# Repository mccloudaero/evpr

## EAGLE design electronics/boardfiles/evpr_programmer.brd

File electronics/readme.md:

# Electronics
Electronics design files for EVPR project.

## Contents
* fabrication - Design files for EVPR fabrication processes, including (eventually) full SOPs for each board
* scripts - Scripts used at various points for automating mass alterations to boardfiles
* info - Various human-readable information about the project, including image versions of boardfiles and BOM
* boadfiles - The actual working boardfiles for the EVPR project.

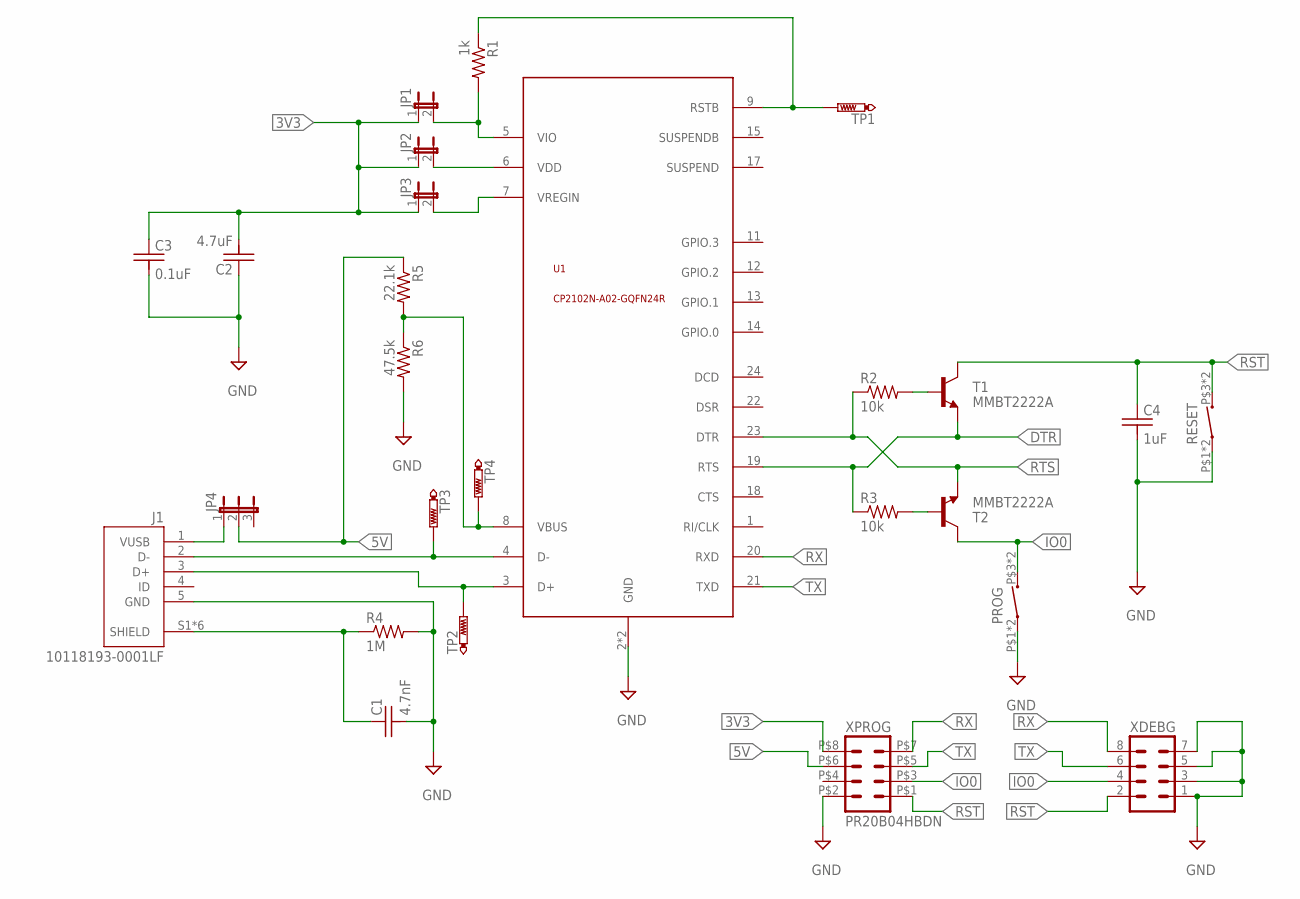
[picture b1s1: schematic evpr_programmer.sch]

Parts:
C1: 4.7nF; C0603
C2: 4.7uF; C0603
C3: 0.1uF; C0603
C4: 1uF; C0603
J1: 10118193-0001LF; FCI_10118193-0001LF
JP1, JP2, JP3: JP1E; JP1
JP4: JP2E; JP2
PROG: MOMENTARY_SWITCH; PTS645
R1: 1k; R0603
R2, R3: 10k; R0603
R4: 1M; R0603
R5: 22.1k; R0603
R6: 47.5k; R0603
RESET: MOMENTARY_SWITCH; PTS645
T1, T2: MMBT2222A; SOT23-BEC
TP1, TP2, TP3, TP4: PTR1TP10R; TP10R
U1: CP2102N-A02-GQFN24R; QFN24-4X4
XDEBG: MA04-2
XPROG: PR20B04HBDN

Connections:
3V3: C2.2, C3.1, JP1.1, JP2.1, JP3.1, XPROG.P$8 (8)
5V: JP4.2, R5.1, XPROG.P$6 (6)
DTR: R3.1, T1.E, U1.19 (RTS)
GND: C1.2, C2.1, C3.2, C4.2, J1.5 (GND), PROG.P$1 (1), PROG.P$2 (1), R4.2, R6.2, RESET.P$1 (1), RESET.P$2 (1), U1.2 (GND), U1.EXP (GND), XDEBG.1, XDEBG.3, XDEBG.5, XDEBG.7, XPROG.P$2 (2)
IO0: PROG.P$3 (2), PROG.P$4 (2), T2.C, XDEBG.4, XPROG.P$3 (3)
unnamed: J1.1 (VUSB), JP4.1
unnamed: JP2.2, U1.6 (VDD)
unnamed: R1.1, TP1.TP, U1.9 (RSTB)
unnamed: JP1.2, R1.2, U1.5 (VIO)
unnamed: C1.1, J1.S1 (SHIELD), J1.S2 (SHIELD), J1.S3 (SHIELD), J1.S4 (SHIELD), J1.S5 (SHIELD), J1.S6 (SHIELD), R4.1
unnamed: R3.2, T2.B
unnamed: R2.2, T1.B
unnamed: J1.3 (D+), TP2.TP, U1.3 (D+)
unnamed: J1.2 (D-), TP3.TP, U1.4 (D-)
unnamed: JP3.2, U1.7 (VREGIN)
unnamed: R5.2, R6.1, TP4.TP, U1.8 (VBUS)
RST: C4.1, RESET.P$3 (2), RESET.P$4 (2), T1.C, XDEBG.2, XPROG.P$1 (1)
RTS: R2.1, T2.E, U1.23 (DTR)
RX: U1.20 (RXD), XDEBG.8, XPROG.P$7 (7)
TX: U1.21 (TXD), XDEBG.6, XPROG.P$5 (5)

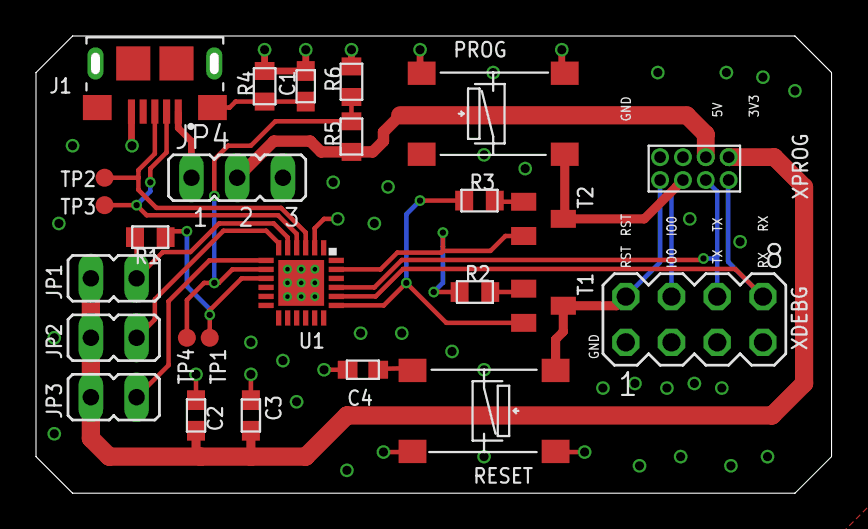
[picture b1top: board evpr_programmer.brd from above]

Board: 2 copper layers, 44.2 x 25.4 mm, 26 parts (0 on the bottom side), 20 nets.

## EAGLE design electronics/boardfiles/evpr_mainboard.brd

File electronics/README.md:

# EVPR electronics

# Compile Notes
Requires ESP-IDF commit (or later):

commit e6afe28bafe5db5ab79fae213f2e8e1ccd9f937c
Merge: ca7da78 7370f29
Author: Jeroen Domburg <jeroen@espressif.com>
Date:   Fri Sep 29 11:20:04 2017 +0800

    Merge branch 'test/unity_print' into 'master'
    
    test: update the format of TEST_ASSERT macro series in ``unity.c``
    
    See merge request !1327

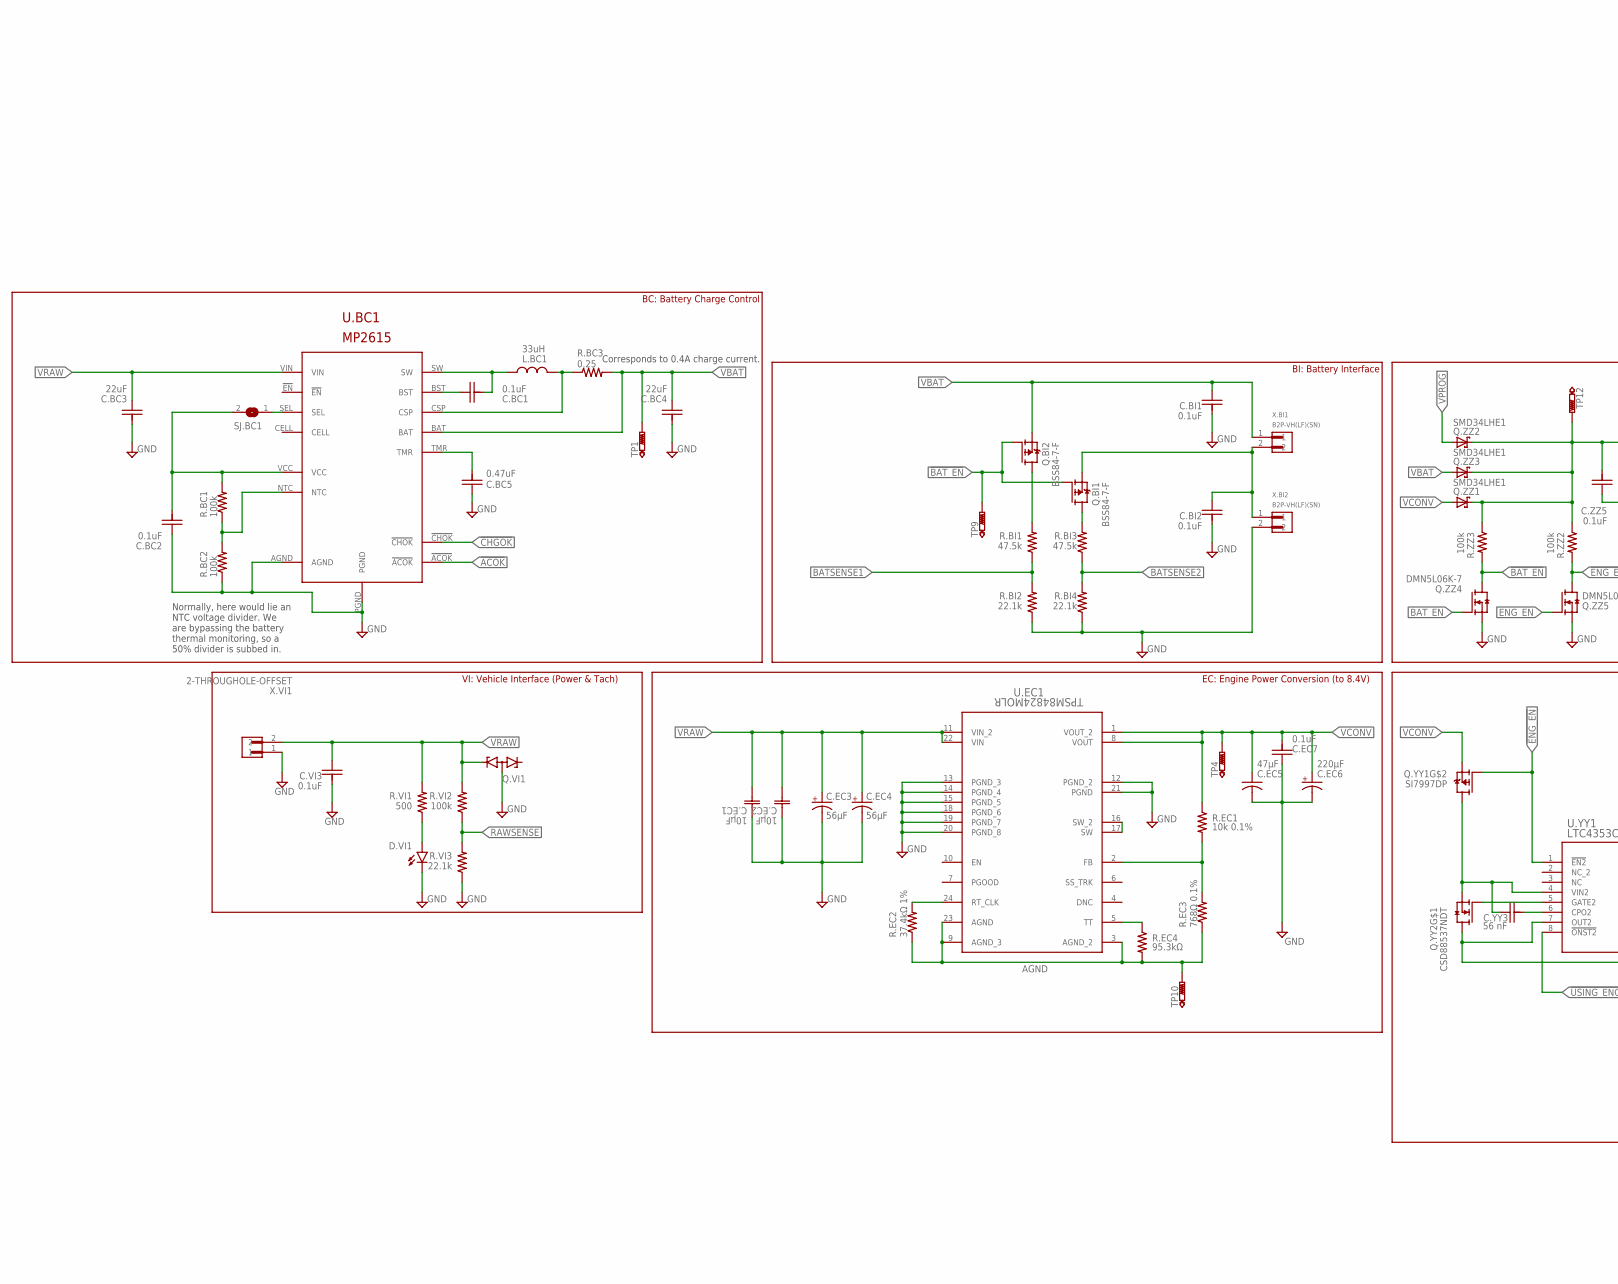
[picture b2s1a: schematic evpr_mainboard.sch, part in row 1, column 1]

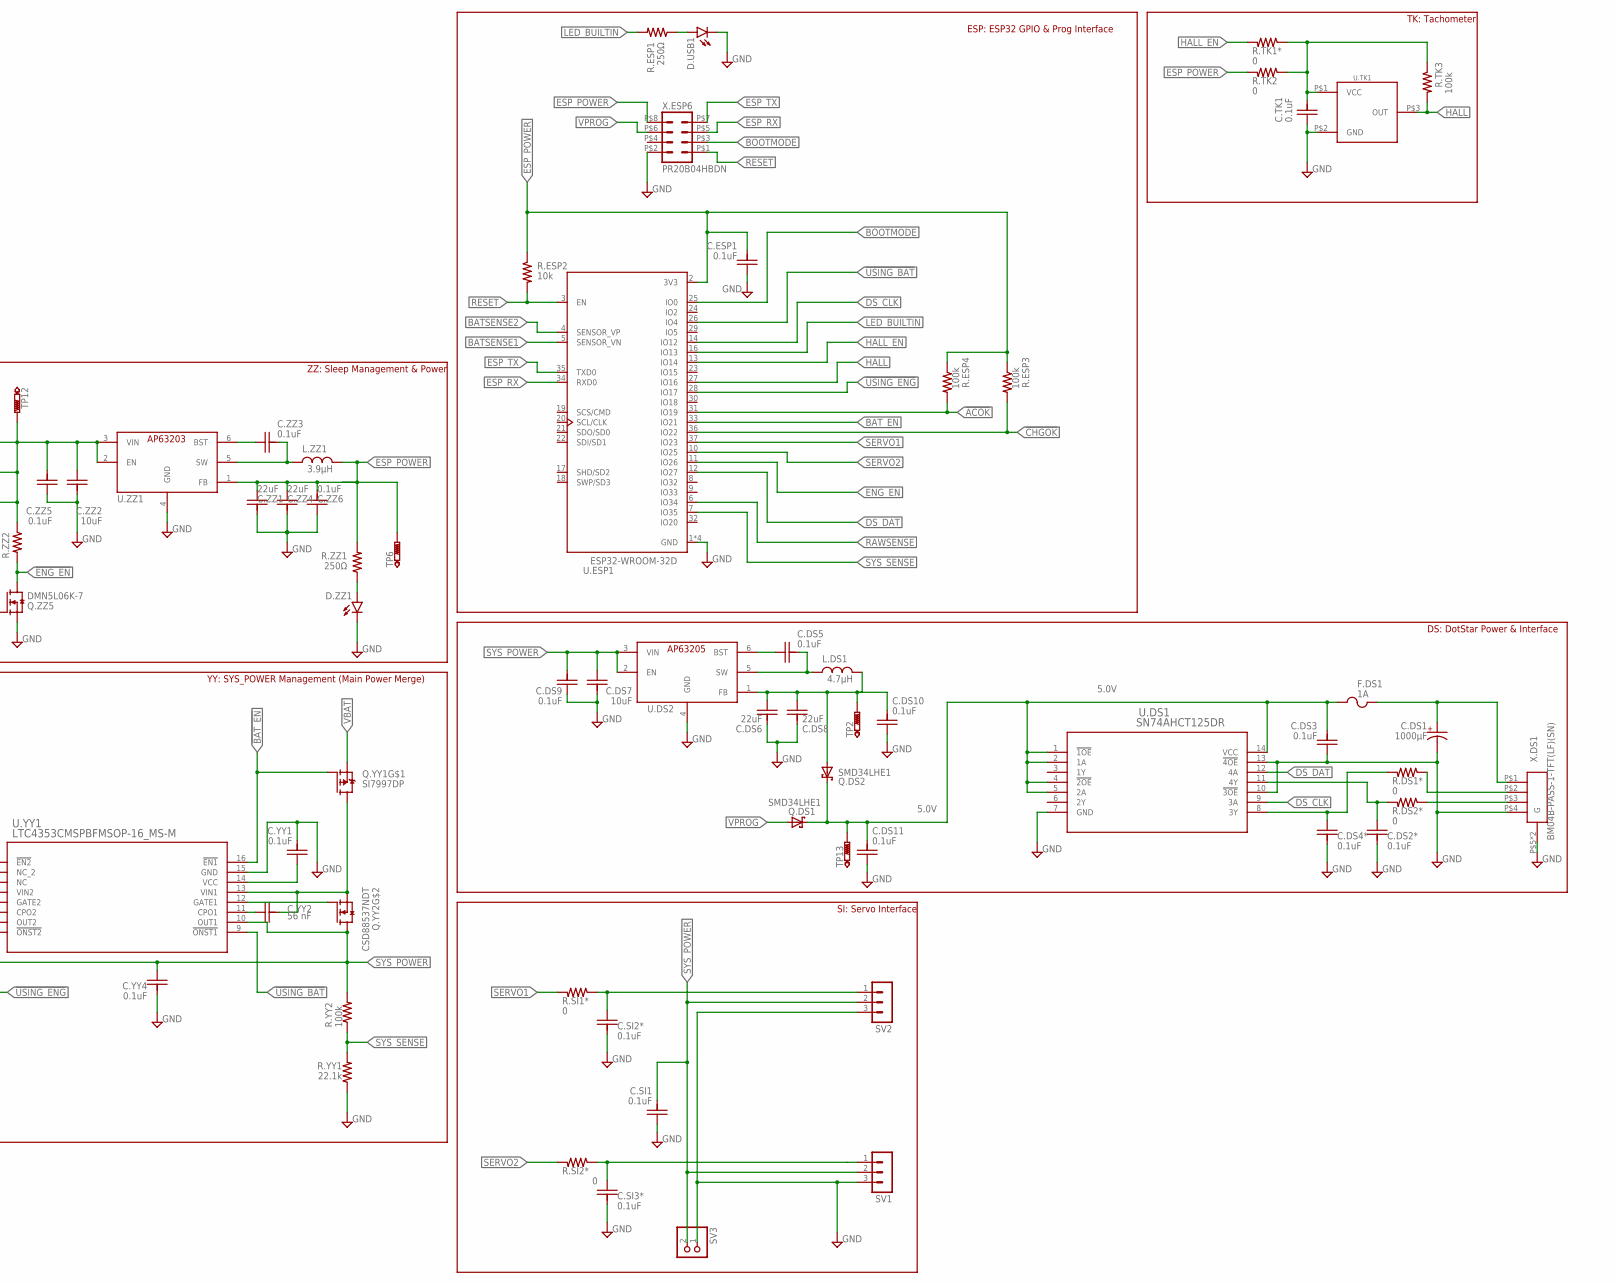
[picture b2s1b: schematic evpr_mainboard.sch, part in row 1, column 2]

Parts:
C.BC1, C.BC2, C.BI1, C.BI2, C.DS2*, C.DS3, C.DS4*, C.DS5, C.DS9, C.DS10, C.DS11, C.EC7, C.ESP1, C.SI1, C.SI2*, C.SI3*, C.TK1, C.VI3, C.YY1, C.YY4, C.ZZ3, C.ZZ5, C.ZZ6: 0.1uF; C0603
C.BC3, C.BC4, C.DS6, C.DS8, C.ZZ1, C.ZZ4: 22uF; C0603
C.BC5: 0.47uF; C0603
C.DS1: 1000µF; 810RADCAN
C.DS7, C.ZZ2: 10uF; C0603
C.EC1, C.EC2: 10µF; CAP_3225
C.EC3, C.EC4: 56µF; OSCON_SVPF_6.3MM
C.EC5: 47µF; C1210
C.EC6: 220µF; C6CYLCAP
C.YY2, C.YY3: 56 nF; C0603
D.USB1, D.VI1, D.ZZ1: LEDCHIP-LED0805; CHIP-LED0805
F.DS1: 1A; C1-M
L.BC1: 33uH; SRN5040TA
L.DS1: 4.7µH; SRR4818A-XXXX
L.ZZ1: 3.9µH; SRR4818A-XXXX
Q.BI1, Q.BI2: BSS84-7-F; SOT23
Q.DS1, Q.DS2, Q.ZZ1, Q.ZZ2, Q.ZZ3: SMD34LHE1; SOD-123HE1
Q.VI1: VESD16A2-03G-G3-08; SOT23
Q.YY1: SI7997DP; POWERPAK_SO8DUAL
Q.YY2: CSD88537NDT; SOIC8
Q.ZZ4, Q.ZZ5: DMN5L06K-7; SOT23
R.BC1, R.BC2, R.ESP3, R.ESP4, R.TK3, R.VI2, R.YY2, R.ZZ2, R.ZZ3: 100k; R0603
R.BC3: 0.25; R0603
R.BI1, R.BI3: 47.5k; R0603
R.BI2, R.BI4, R.VI3, R.YY1: 22.1k; R0603
R.DS1*, R.DS2*, R.SI1*, R.SI2*, R.TK1*, R.TK2: 0; R0603
R.EC1: 10k 0.1%; R0603
R.EC2: 37.4kΩ 1%; R0603
R.EC3: 768Ω 0.1%; R0603
R.EC4: 95.3kΩ; R0603
R.ESP1, R.ZZ1: 250Ω; R0603
R.ESP2: 10k; R0603
R.VI1: 500; R0603
SJ.BC1: SJ
SV1, SV2: MA03-1
SV3: PINHD-1X2; 1X02
TP1, TP2, TP4, TP6, TP9, TP10, TP12, TP13: PTR1TP10R; TP10R
U.BC1: MP2615; QFN16
U.DS1: SN74AHCT125DR; D14
U.DS2: AP63205; TSOT23-6
U.EC1: TPSM84824MOLR; MOL0024A
U.ESP1: ESP32-WROOM-32D; MODULE_ESP32-WROOM-32D
U.TK1: HALLEFFECT; 1.27MMHALLEFECT
U.YY1: LTC4353CMSPBFMSOP-16_MS-M; MSOP-16_MS-M
U.ZZ1: AP63203; TSOT23-6
X.BI1, X.BI2: B2P-VH(LF)(SN)
X.DS1: BM04B-PASS-1-TFT(LF)(SN)
X.ESP6: PR20B04HBDN
X.VI1: 2-THROUGHOLE-OFFSET; 2-THROUGH-HOLE-LARGE-OFFSET

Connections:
5.0V: C.DS3.2, C.DS11.2, F.DS1.1, Q.DS1.C, Q.DS2.C, TP13.TP, U.DS1.1 (!1OE), U.DS1.2 (1A), U.DS1.4 (!2OE), U.DS1.5 (2A), U.DS1.14 (VCC)
!ACOK: R.ESP4.2, U.BC1.!ACOK, U.ESP1.31 (IO19)
!BAT_EN: Q.BI1.1 (G), Q.BI2.1 (G), Q.YY1.P$2 (G), Q.ZZ4.3 (D), R.ZZ3.2, TP9.TP, U.YY1.16 (!EN1)
!CHGOK: R.ESP3.2, U.BC1.!CHOK, U.ESP1.36 (IO22)
!ENG_EN: Q.YY1.P$4 (G), Q.ZZ5.3 (D), R.ZZ2.2, U.YY1.1 (!EN2)
!USING_BAT: U.ESP1.26 (IO4), U.YY1.9 (!ONST1)
!USING_ENG: U.ESP1.28 (IO17), U.YY1.8 (!ONST2)
AGND: R.EC2.1, R.EC3.1, R.EC4.2, TP10.TP, U.EC1.3 (AGND_2), U.EC1.9 (AGND_3), U.EC1.23 (AGND)
BATSENSE1: R.BI1.1, R.BI2.2, U.ESP1.5 (SENSOR_VN)
BATSENSE2: R.BI3.1, R.BI4.2, U.ESP1.4 (SENSOR_VP)
BAT_EN: Q.ZZ4.1 (G), U.ESP1.33 (IO21)
BOOTMODE: U.ESP1.25 (IO0), X.ESP6.P$3 (3)
DS_CLK: U.DS1.9 (3A), U.ESP1.14 (IO12)
DS_DAT: U.DS1.12 (4A), U.ESP1.12 (IO27)
ENG_EN: Q.ZZ5.1 (G), U.ESP1.11 (IO26)
ESP_POWER: C.ESP1.2, C.ZZ1.1, C.ZZ4.1, C.ZZ6.2, L.ZZ1.P$2 (2), R.ESP2.1, R.ESP3.1, R.ESP4.1, R.TK2.2, R.ZZ1.2, TP6.TP, U.ESP1.2 (3V3), U.ZZ1.1 (FB), X.ESP6.P$8 (8)
ESP_RX: U.ESP1.34 (RXD0), X.ESP6.P$5 (5)
ESP_TX: U.ESP1.35 (TXD0), X.ESP6.P$7 (7)
GND: C.BC2.1, C.BC3.2, C.BC4.2, C.BC5.1, C.BI1.2, C.BI2.2, C.DS1.C$2 (-), C.DS2*.2, C.DS3.1, C.DS4*.2, C.DS6.2, C.DS7.2, C.DS8.2, C.DS9.1, C.DS10.1, C.DS11.1, C.EC1.1, C.EC2.1, C.EC3.-, C.EC4.-, C.EC5.2, C.EC6.P$1 (-), C.EC7.1, C.ESP1.1, C.SI1.1, C.SI2*.2, C.SI3*.2, C.TK1.1, C.VI3.2, C.YY1.2, C.YY4.2, C.ZZ1.2, C.ZZ2.2, C.ZZ4.2, C.ZZ5.1, C.ZZ6.1, D.USB1.C, D.VI1.C, D.ZZ1.C, Q.VI1.3 (AA), Q.ZZ4.2 (S), Q.ZZ5.2 (S), R.BC2.1, R.BI2.1, R.BI4.1, R.VI3.1, R.YY1.1, SV1.3, SV2.3, SV3.1, U.BC1.AGND, U.BC1.PGND, U.DS1.7 (GND), U.DS1.10 (!3OE), U.DS1.13 (!4OE), U.DS2.4 (GND), U.EC1.12 (PGND_2), U.EC1.13 (PGND_3), U.EC1.14 (PGND_4), U.EC1.15 (PGND_5), U.EC1.18 (PGND_6), U.EC1.19 (PGND_7), U.EC1.20 (PGND_8), U.EC1.21 (PGND), U.ESP1.1 (GND), U.ESP1.15 (GND), U.ESP1.38 (GND), U.ESP1.39 (GND), U.TK1.P$2 (GND), U.YY1.15 (GND), U.ZZ1.4 (GND), X.BI2.2, X.DS1.P$4 (4), X.DS1.P$5 (G), X.DS1.P$6 (G), X.ESP6.P$2 (2), X.VI1.1
HALL: R.TK3.2, U.ESP1.27 (IO16), U.TK1.P$3 (OUT)
HALL_EN: R.TK1*.2, U.ESP1.13 (IO14)
LED_BUILTIN: R.ESP1.2, U.ESP1.16 (IO13)
unnamed: C.TK1.2, R.TK1*.1, R.TK2.1, R.TK3.1, U.TK1.P$1 (VCC)
unnamed: R.EC1.2, R.EC3.2, U.EC1.2 (FB)
unnamed: Q.YY2.4 (G), U.YY1.12 (GATE1)
unnamed: C.YY3.1, Q.YY1.D$2A (D), Q.YY2.1 (S), U.YY1.4 (VIN2)
unnamed: C.YY2.2, Q.YY1.D$1B (D), Q.YY2.3 (S), U.YY1.13 (VIN1)
unnamed: C.BC5.2, U.BC1.TMR
unnamed: C.BI2.1, Q.BI1.2 (S), X.BI1.2, X.BI2.1
unnamed: C.ZZ2.1, C.ZZ5.2, Q.ZZ1.C, Q.ZZ2.C, Q.ZZ3.C, R.ZZ2.1, R.ZZ3.1, TP12.TP, U.ZZ1.2 (EN), U.ZZ1.3 (VIN)
unnamed: Q.YY2.2 (G), U.YY1.5 (GATE2)
unnamed: C.SI2*.1, R.SI1*.1, SV2.1
unnamed: C.SI3*.1, R.SI2*.1, SV1.1
unnamed: Q.BI2.3 (D), R.BI1.2
unnamed: C.ZZ3.1, U.ZZ1.6 (BST)
unnamed: U.EC1.16 (SW_2), U.EC1.17 (SW)
unnamed: R.EC2.2, U.EC1.24 (RT_CLK)
unnamed: C.DS2*.1, R.DS2*.2, U.DS1.11 (4Y)
unnamed: D.VI1.A, R.VI1.1
unnamed: D.USB1.A, R.ESP1.1
unnamed: C.ZZ3.2, L.ZZ1.P$1 (1), U.ZZ1.5 (SW)
unnamed: C.DS4*.1, R.DS1*.2, U.DS1.8 (3Y)
unnamed: C.DS1.A$1 (+), F.DS1.2, X.DS1.P$1 (1)
unnamed: C.DS5.1, U.DS2.6 (BST)
unnamed: R.DS1*.1, X.DS1.P$2 (2)
unnamed: R.EC4.1, U.EC1.5 (TT)
unnamed: C.YY1.1, U.YY1.14 (VCC)
unnamed: Q.BI1.3 (D), R.BI3.2
unnamed: D.ZZ1.A, R.ZZ1.1
unnamed: C.YY2.1, U.YY1.11 (CPO1)
unnamed: C.YY3.2, U.YY1.6 (CPO2)
unnamed: R.DS2*.1, X.DS1.P$3 (3)
unnamed: R.BC1.1, R.BC2.2, U.BC1.NTC
unnamed: C.DS5.2, L.DS1.P$1 (1), U.DS2.5 (SW)
unnamed: C.DS6.1, C.DS8.1, C.DS10.2, L.DS1.P$2 (2), Q.DS2.A, TP2.TP, U.DS2.1 (FB)
unnamed: C.BC2.2, R.BC1.2, SJ.BC1.2, U.BC1.VCC
unnamed: L.BC1.P$2 (2), R.BC3.1, U.BC1.CSP
unnamed: SJ.BC1.1, U.BC1.SEL
unnamed: C.BC1.1, U.BC1.BST
unnamed: C.BC1.2, L.BC1.P$1 (1), U.BC1.SW
RAWSENSE: R.VI2.1, R.VI3.2, U.ESP1.6 (IO34)
RESET: R.ESP2.2, U.ESP1.3 (EN), X.ESP6.P$1 (1)
SERVO1: R.SI1*.2, U.ESP1.37 (IO23)
SERVO2: R.SI2*.2, U.ESP1.10 (IO25)
SYS_POWER: C.DS7.1, C.DS9.2, C.SI1.2, C.YY4.1, Q.YY2.5 (D), Q.YY2.6 (D), Q.YY2.7 (D), Q.YY2.8 (D), R.YY2.2, SV1.2, SV2.2, SV3.2, U.DS2.2 (EN), U.DS2.3 (VIN), U.YY1.7 (OUT2), U.YY1.10 (OUT1)
SYS_SENSE: R.YY1.2, R.YY2.1, U.ESP1.7 (IO35)
VBAT: C.BC4.1, C.BI1.1, Q.BI2.2 (S), Q.YY1.P$1 (S), Q.ZZ3.A, R.BC3.2, TP1.TP, U.BC1.BAT, X.BI1.1
VCONV: C.EC5.1, C.EC6.P$2 (+), C.EC7.2, Q.YY1.P$3 (S), Q.ZZ1.A, R.EC1.1, TP4.TP, U.EC1.1 (VOUT_2), U.EC1.8 (VOUT)
VPROG: Q.DS1.A, Q.ZZ2.A, X.ESP6.P$6 (6)
VRAW: C.BC3.1, C.EC1.2, C.EC2.2, C.EC3.+, C.EC4.+, C.VI3.1, Q.VI1.1 (K2), R.VI1.2, R.VI2.2, U.BC1.VIN, U.EC1.11 (VIN_2), U.EC1.22 (VIN), X.VI1.2

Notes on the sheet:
VI: Vehicle Interface (Power & Tach)
EC: Engine Power Conversion (to 8.4V)
BC: Battery Charge Control
BI: Battery Interface
YY: SYS_POWER Management (Main Power Merge)
DS: DotStar Power & Interface
SI: Servo Interface
ESP: ESP32 GPIO & Prog Interface
ZZ: Sleep Management & Power
Normally, here would lie an NTC voltage divider. We are bypassing the battery thermal monitoring, so a 50% divider is subbed in.
Corresponds to 0.4A charge current.
TK: Tachometer

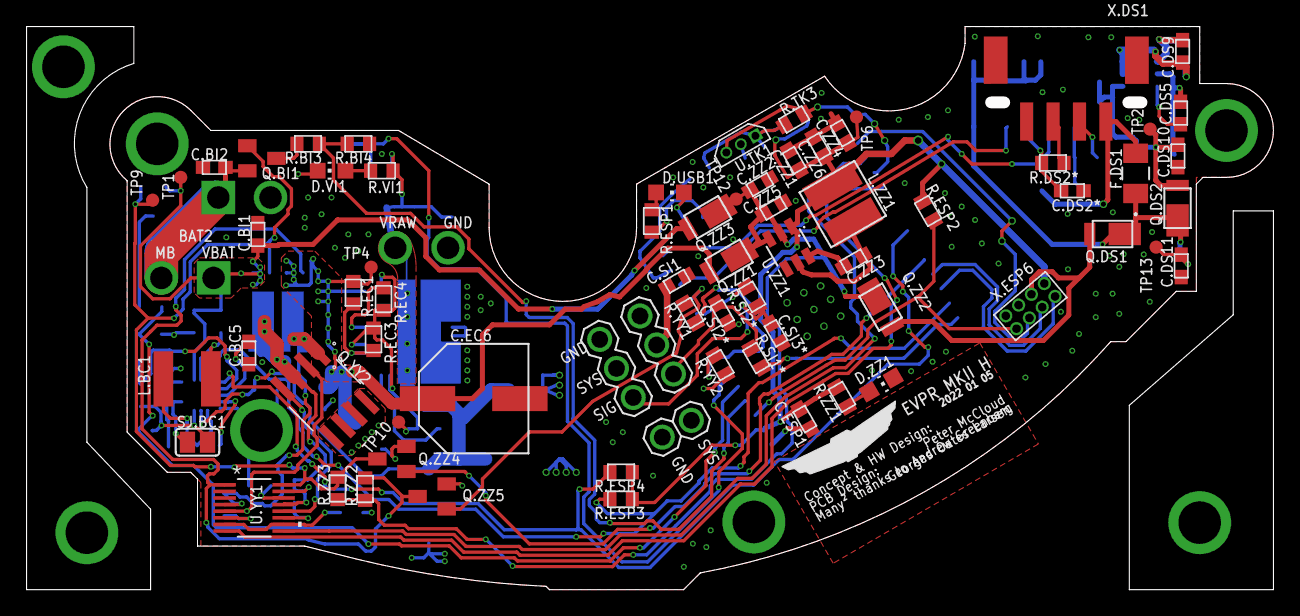
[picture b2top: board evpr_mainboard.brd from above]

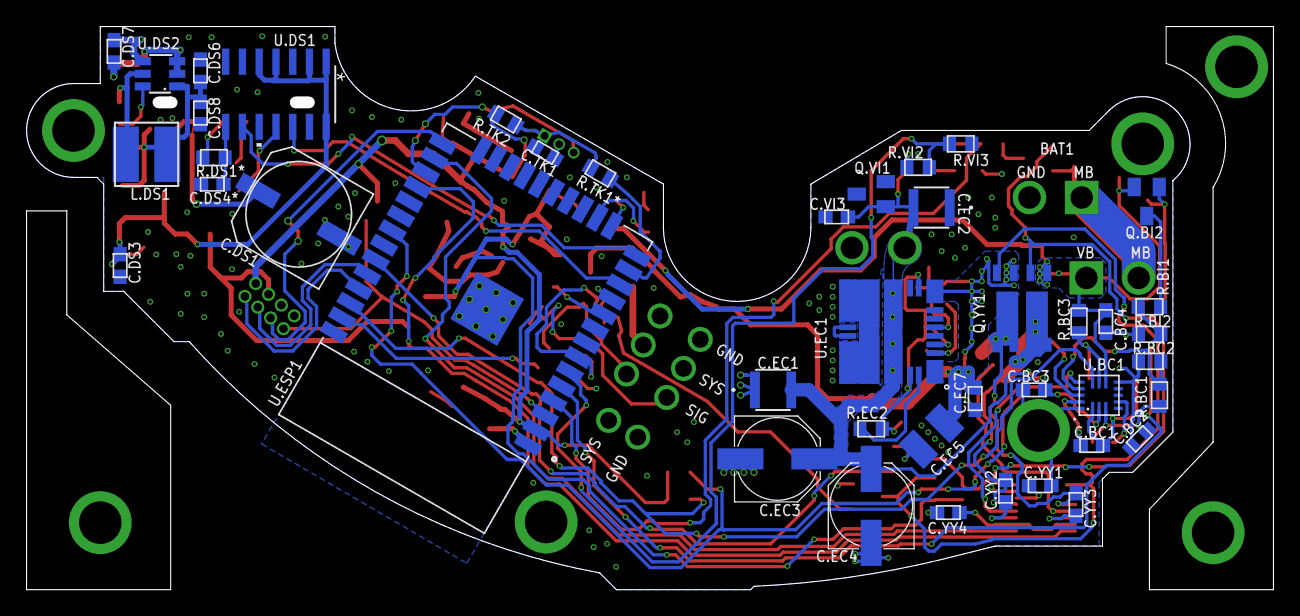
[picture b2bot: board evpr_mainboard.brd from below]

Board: 4 copper layers, 94.5 x 42.7 mm, 115 parts (43 on the bottom side), 70 nets.

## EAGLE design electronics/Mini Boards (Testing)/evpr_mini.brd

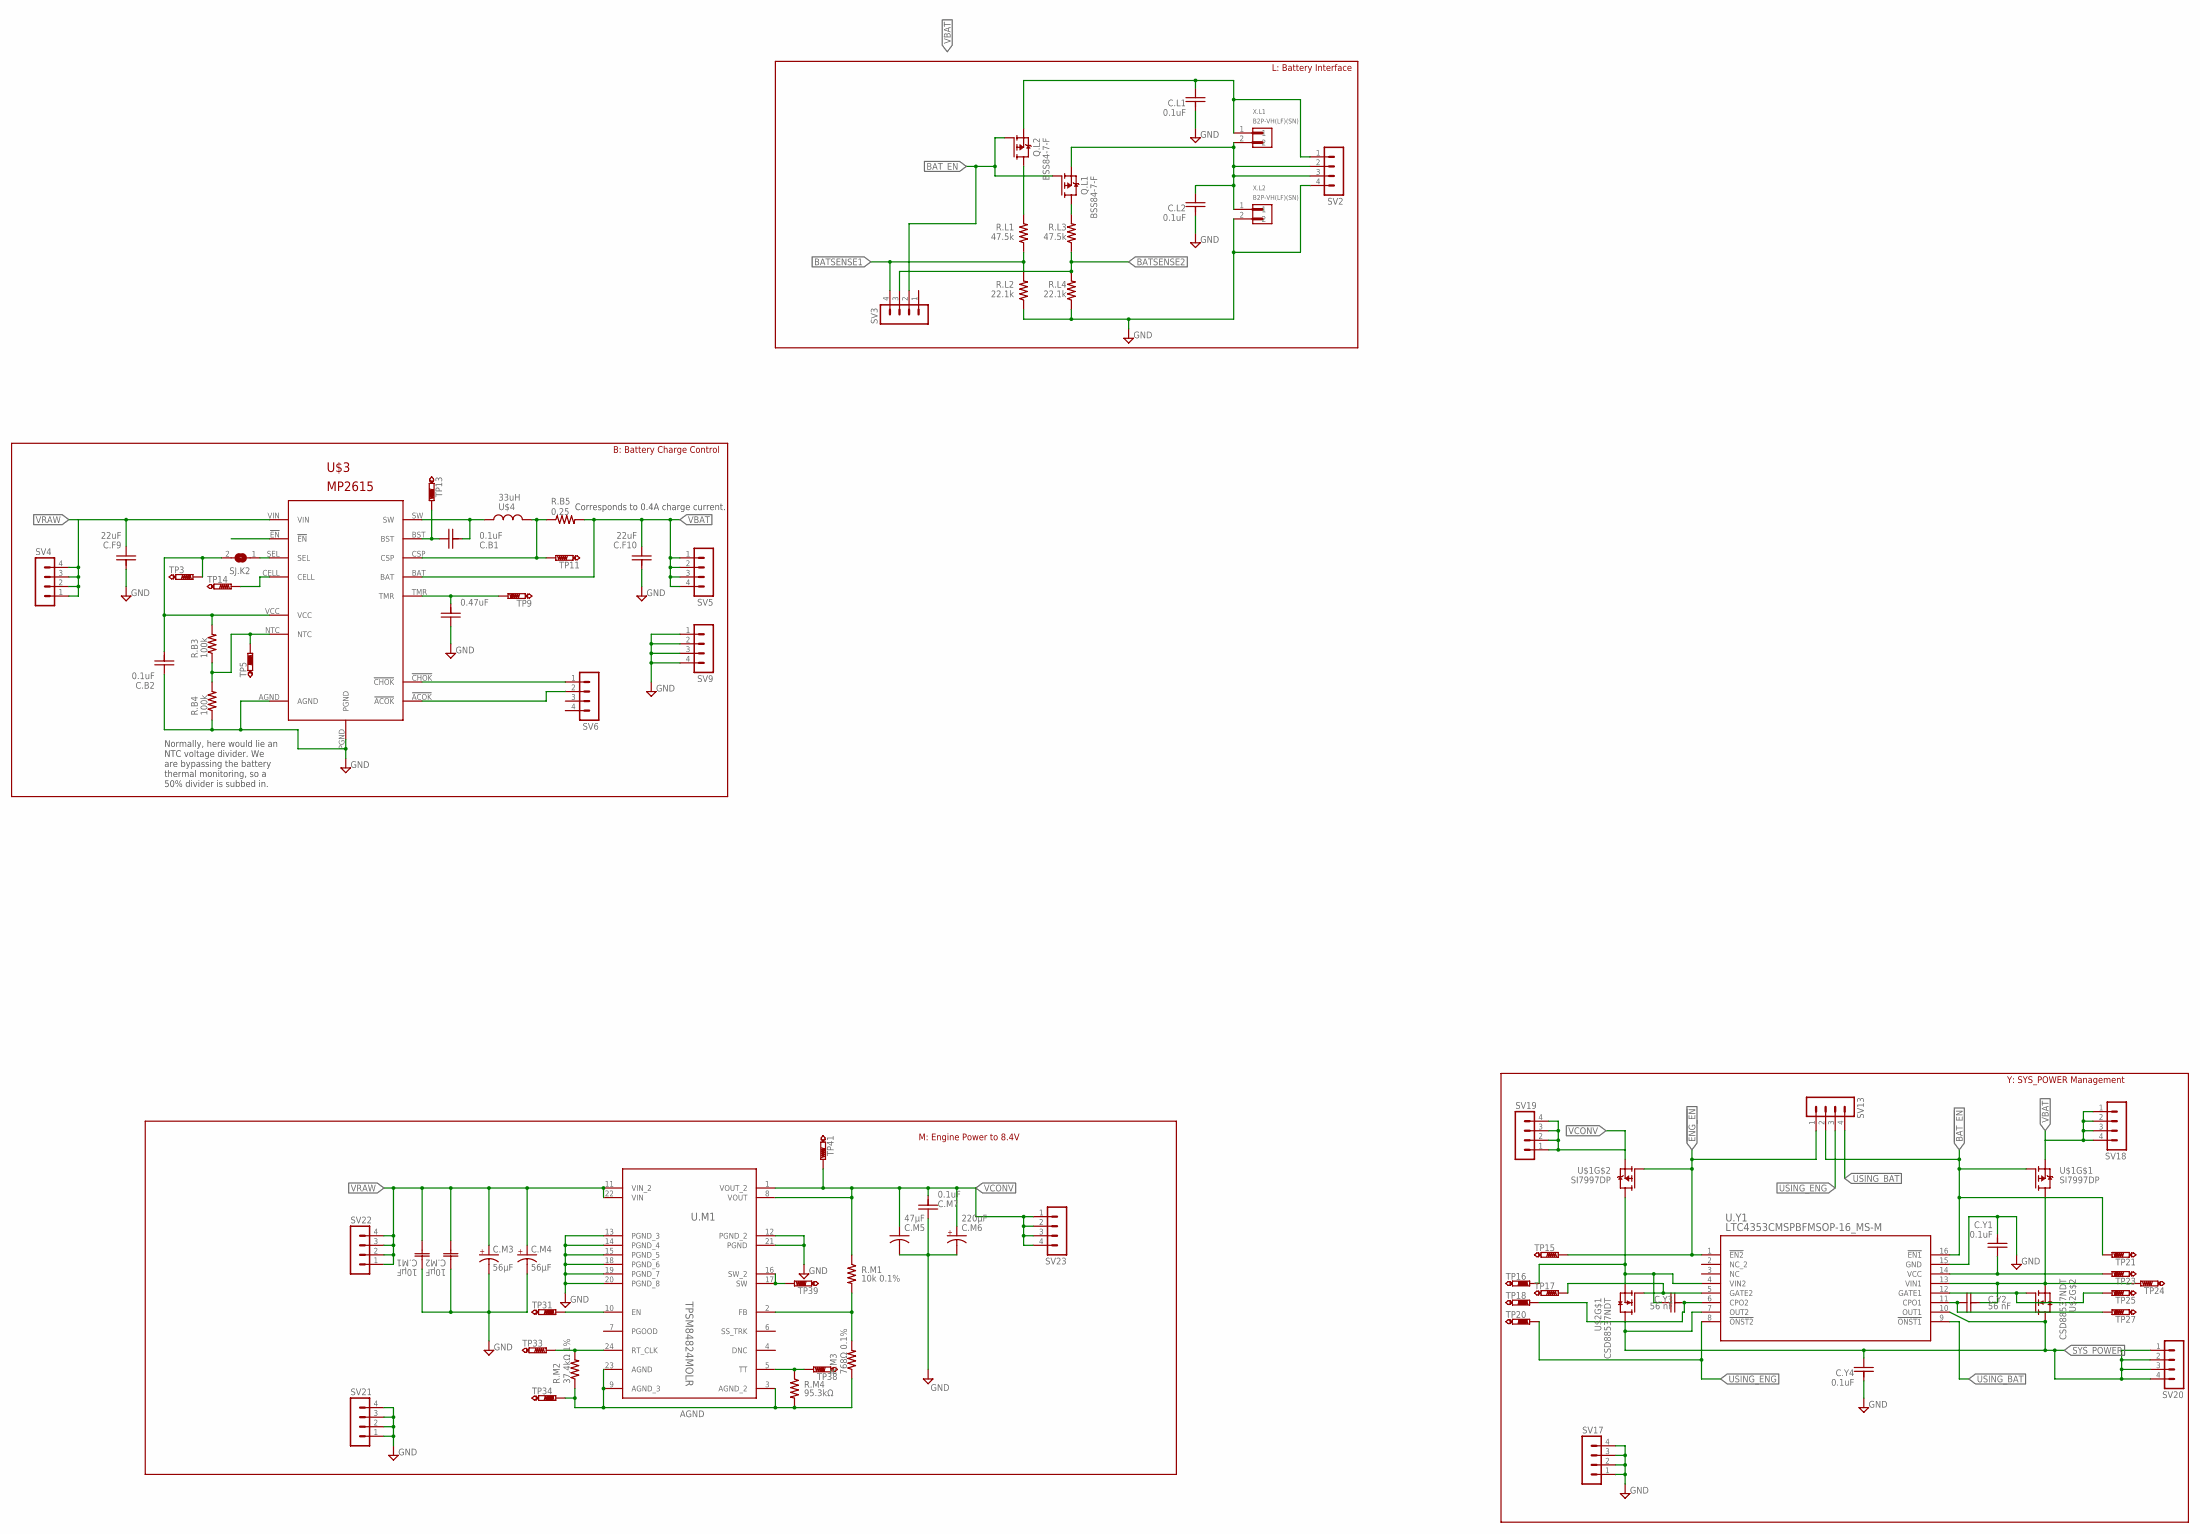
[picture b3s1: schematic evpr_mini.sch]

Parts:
C.B1, C.B2, C.L1, C.L2, C.M7, C.Y1, C.Y4: 0.1uF; C0603
C.F9, C.F10: 22uF; C0603
C.J3: 0.47uF; C0603
C.M1, C.M2: 10µF; CAP_3225
C.M3, C.M4: 56µF; OSCON_SVPF_6.3MM
C.M5: 47µF; C1210
C.M6: 220µF; C6CYLCAP
C.Y2, C.Y3: 56 nF; C0603
Q.L1, Q.L2: BSS84-7-F; SOT23
R.B3, R.B4: 100k; R0603
R.B5: 0.25; R0603
R.L1, R.L3: 47.5k; R0603
R.L2, R.L4: 22.1k; R0603
R.M1: 10k 0.1%; R0603
R.M2: 37.4kΩ 1%; R0603
R.M3: 768Ω 0.1%; R0603
R.M4: 95.3kΩ; R0603
SJ.K2: SJ
SV2, SV3, SV4, SV5, SV6, SV9, SV13, SV17, SV18, SV19, SV20, SV21, SV22, SV23: MA04-1
TP3, TP5, TP9, TP11, TP13, TP14, TP15, TP16, TP17, TP18, TP20, TP21, TP23, TP24, TP25, TP27, TP31, TP33, TP34, TP38, TP39, TP41: PTR1TP10R; TP10R
U$1: SI7997DP; POWERPAK_SO8DUAL
U$2: CSD88537NDT; SOIC8
U$3: MP2615; QFN16
U$4: 33uH; SRN5040TA
U.M1: TPSM84824MOLR; MOL0024A
U.Y1: LTC4353CMSPBFMSOP-16_MS-M; MSOP-16_MS-M
X.L1, X.L2: B2P-VH(LF)(SN); JST_B2P-VH(LF)(SN)

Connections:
!ACOK: SV6.2, U$3.!ACOK
!BAT_EN: Q.L1.1 (G), Q.L2.1 (G), SV3.2, SV13.2, TP21.TP, U$1.P$2 (G), U.Y1.16 (!EN1)
!CHGOK: SV6.1, U$3.!CHOK
!ENG_EN: SV13.1, TP15.TP, U$1.P$4 (G), U.Y1.1 (!EN2)
AGND: R.M2.1, R.M3.1, R.M4.2, TP34.TP, U.M1.3 (AGND_2), U.M1.9 (AGND_3), U.M1.23 (AGND)
BATSENSE1: R.L1.1, R.L2.2, SV3.4
BATSENSE2: R.L3.1, R.L4.2, SV3.3
GND: C.B2.1, C.F9.2, C.F10.2, C.J3.1, C.L1.2, C.L2.2, C.M1.1, C.M2.1, C.M3.-, C.M4.-, C.M5.2, C.M6.P$1 (-), C.M7.1, C.Y1.2, C.Y4.2, R.B4.1, R.L2.1, R.L4.1, SV2.4, SV9.1, SV9.2, SV9.3, SV9.4, SV17.1, SV17.2, SV17.3, SV17.4, SV21.1, SV21.2, SV21.3, SV21.4, U$3.AGND, U$3.PGND, U.M1.12 (PGND_2), U.M1.13 (PGND_3), U.M1.14 (PGND_4), U.M1.15 (PGND_5), U.M1.18 (PGND_6), U.M1.19 (PGND_7), U.M1.20 (PGND_8), U.M1.21 (PGND), U.Y1.15 (GND), X.L2.2
unnamed: TP14.TP, U$3.CELL
unnamed: R.M1.2, R.M3.2, U.M1.2 (FB)
unnamed: TP25.TP, U$2.4 (G), U.Y1.12 (GATE1)
unnamed: C.Y3.1, TP16.TP, U$1.D$2A (D), U$2.1 (S), U.Y1.4 (VIN2)
unnamed: C.Y2.2, TP24.TP, U$1.D$1B (D), U$2.3 (S), U.Y1.13 (VIN1)
unnamed: C.J3.2, TP9.TP, U$3.TMR
unnamed: C.L2.1, Q.L1.2 (S), SV2.2, SV2.3, X.L1.2, X.L2.1
unnamed: TP17.TP, U$2.2 (G), U.Y1.5 (GATE2)
unnamed: TP31.TP, U.M1.10 (EN)
unnamed: Q.L2.3 (D), R.L1.2
unnamed: TP39.TP, U.M1.16 (SW_2), U.M1.17 (SW)
unnamed: R.M2.2, TP33.TP, U.M1.24 (RT_CLK)
unnamed: R.M4.1, TP38.TP, U.M1.5 (TT)
unnamed: C.Y1.1, TP23.TP, U.Y1.14 (VCC)
unnamed: Q.L1.3 (D), R.L3.2
unnamed: C.Y2.1, TP27.TP, U.Y1.11 (CPO1)
unnamed: C.Y3.2, TP18.TP, U.Y1.6 (CPO2)
unnamed: R.B3.1, R.B4.2, TP5.TP, U$3.NTC
unnamed: C.B2.2, R.B3.2, SJ.K2.2, TP3.TP, U$3.VCC
unnamed: R.B5.1, TP11.TP, U$3.CSP, U$4.P$2 (2)
unnamed: SJ.K2.1, U$3.SEL
unnamed: C.B1.1, TP13.TP, U$3.BST
unnamed: C.B1.2, U$3.SW, U$4.P$1 (1)
SYS_POWER: C.Y4.1, SV20.1, SV20.2, SV20.3, SV20.4, U$2.5 (D), U$2.6 (D), U$2.7 (D), U$2.8 (D), U.Y1.7 (OUT2), U.Y1.10 (OUT1)
USING_BAT: SV13.4, U.Y1.9 (!ONST1)
USING_ENG: SV13.3, TP20.TP, U.Y1.8 (!ONST2)
VBAT: C.F10.1, C.L1.1, Q.L2.2 (S), R.B5.2, SV2.1, SV5.1, SV5.2, SV5.3, SV5.4, SV18.1, SV18.2, SV18.3, SV18.4, U$1.P$1 (S), U$3.BAT, X.L1.1
VCONV: C.M5.1, C.M6.P$2 (+), C.M7.2, R.M1.1, SV19.1, SV19.2, SV19.3, SV19.4, SV23.1, SV23.2, SV23.3, SV23.4, TP41.TP, U$1.P$3 (S), U.M1.1 (VOUT_2), U.M1.8 (VOUT)
VRAW: C.F9.1, C.M1.2, C.M2.2, C.M3.+, C.M4.+, SV4.1, SV4.2, SV4.3, SV4.4, SV22.1, SV22.2, SV22.3, SV22.4, U$3.VIN, U.M1.11 (VIN_2), U.M1.22 (VIN)

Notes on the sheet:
M: Engine Power to 8.4V
B: Battery Charge Control
L: Battery Interface
Y: SYS_POWER Management
Normally, here would lie an NTC voltage divider. We are bypassing the battery thermal monitoring, so a 50% divider is subbed in.
Corresponds to 0.4A charge current.

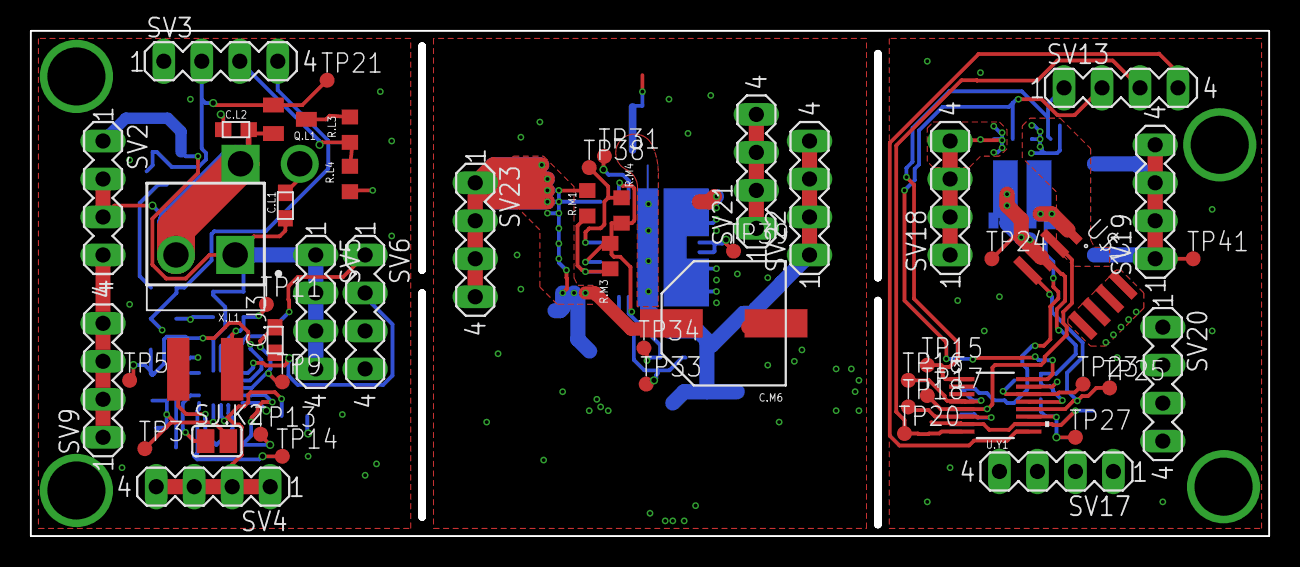
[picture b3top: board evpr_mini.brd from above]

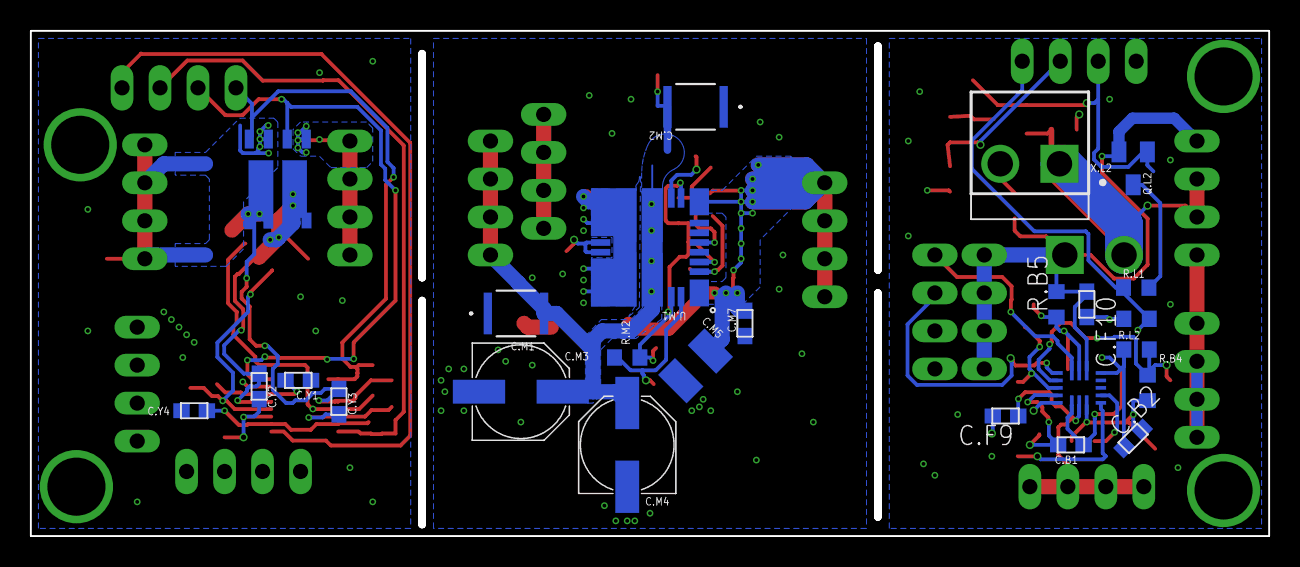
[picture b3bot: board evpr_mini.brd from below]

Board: 4 copper layers, 82.8 x 33.8 mm, 76 parts (25 on the bottom side), 37 nets.

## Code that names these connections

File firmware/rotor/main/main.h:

#define TAG "rotor"
#define ROTOR_NUM CONFIG_ROTOR_NUM
#define ROTOR_MODE CONFIG_ROTOR_MODE

// WIFI
#define WIFI_SSID CONFIG_WIFI_SSID
#define WIFI_PWD CONFIG_WIFI_PASSWORD

// PWM_PINS 
#define PWMA_PIN CONFIG_PWMA_PIN
#define PWMB_PIN CONFIG_PWMB_PIN

// DOTSTAR_PINS 
#define DSTAR_SDA_PIN CONFIG_DSTAR_SDA_PIN
#define DSTAR_CLK_PIN CONFIG_DSTAR_CLK_PIN

// Status
#define BLINK_GPIO CONFIG_BLINK_GPIO
#define USING_BAT_GPIO CONFIG_USING_BAT_GPIO
#define USING_ENG_GPIO CONFIG_USING_ENG_GPIO
#define TACH_GPIO CONFIG_TACH_GPIO

// Enable
#define BAT_EN_GPIO CONFIG_BAT_EN_GPIO
#define ENG_EN_GPIO CONFIG_ENG_EN_GPIO

#define BUF_SIZE (512)

//parser
typedef enum {
	HEAD,
	LEN,
	ID,
	DATA,
	CRC,
	END,
} PARSER_STATE;

typedef  struct {
	uint8_t head;
	uint8_t payload_len;
	uint8_t payload[16];  //For now just using 8 bytes
	uint8_t crc_data;     //To be implemented
} pwm_packet;
